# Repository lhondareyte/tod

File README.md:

## Top Octave Frequency generator

An  attempt to build a top octave divider. This can also be used to make any static prescaler.

## Restrictions

### DC Characteristics

Original MOSTEK chips require a supply voltage of ~15v (Max 16v). Input clock voltage must be between 0v and Vss -1v min. To avoid this, a TTL compatible master clock is include in schematic (Typical clock frequency is 2.00024 MHz).

### Duty cycle

MOSTEK chips differs in their number of dividers and duty cycle :

* MK50240 : 50% - 13 dividers (239 to 478)
* MK50241 : 30% - 13 dividers (239 to 478)
* MK50242 : 50% - 12 dividers (239 to 451)

This emulation only generate a (almost) 50% duty cycle. Thereby,  MK50241 model is not supported since the timbre will be affected. 

## Power consumption

Original MOSTEK chips sink 24mA@15V : 0.36w Typ. (Max 37mA@15V = 0.56W). You need 13 attiny4/13 to emulate a MK50240 (12 for a MK50242). Total power consumption for 13 ATtiny13 is about 30mA@5V (Not include clock circuitry).

## TODO

* Support 30% duty cycle

## Other use

The script `genedivider.pl` can be use to generate assembly code for any static prescaler. For example, to build a `by 42` prescaler:

    ./genedivider.pl 42 > divide.S

If an overflow/underflow occurs you can try to adjust `$loop` variable:

    ./genedivider.pl 10000 200 > divide.S

Warning, the script do not check the generated code size.

## Programming the attiny4

The ATtiny4 require a programmer that is compatible with the TPI mode (Tiny Programming Interface). 

To flash one divider with `avrdude`,  connect the attiny to the programmer as follow:

     USBASP               ATTINY
       +5v <-------------> +5v     (pin 5)
       gnd <-------------> gnd     (pin 2)
     reset <-------------> reset   (pin 6)
      MOSI <-------------> TPIDATA (pin 1)
       CLK <-------------> TPICLK  (pin 3)

then

    avrdude -c usbasp -p t4 -U flash:w:437.hex

and apply fuse configuration

    avrdude -c usbasp -p t4 -U BYTE0:w:0xfa:m

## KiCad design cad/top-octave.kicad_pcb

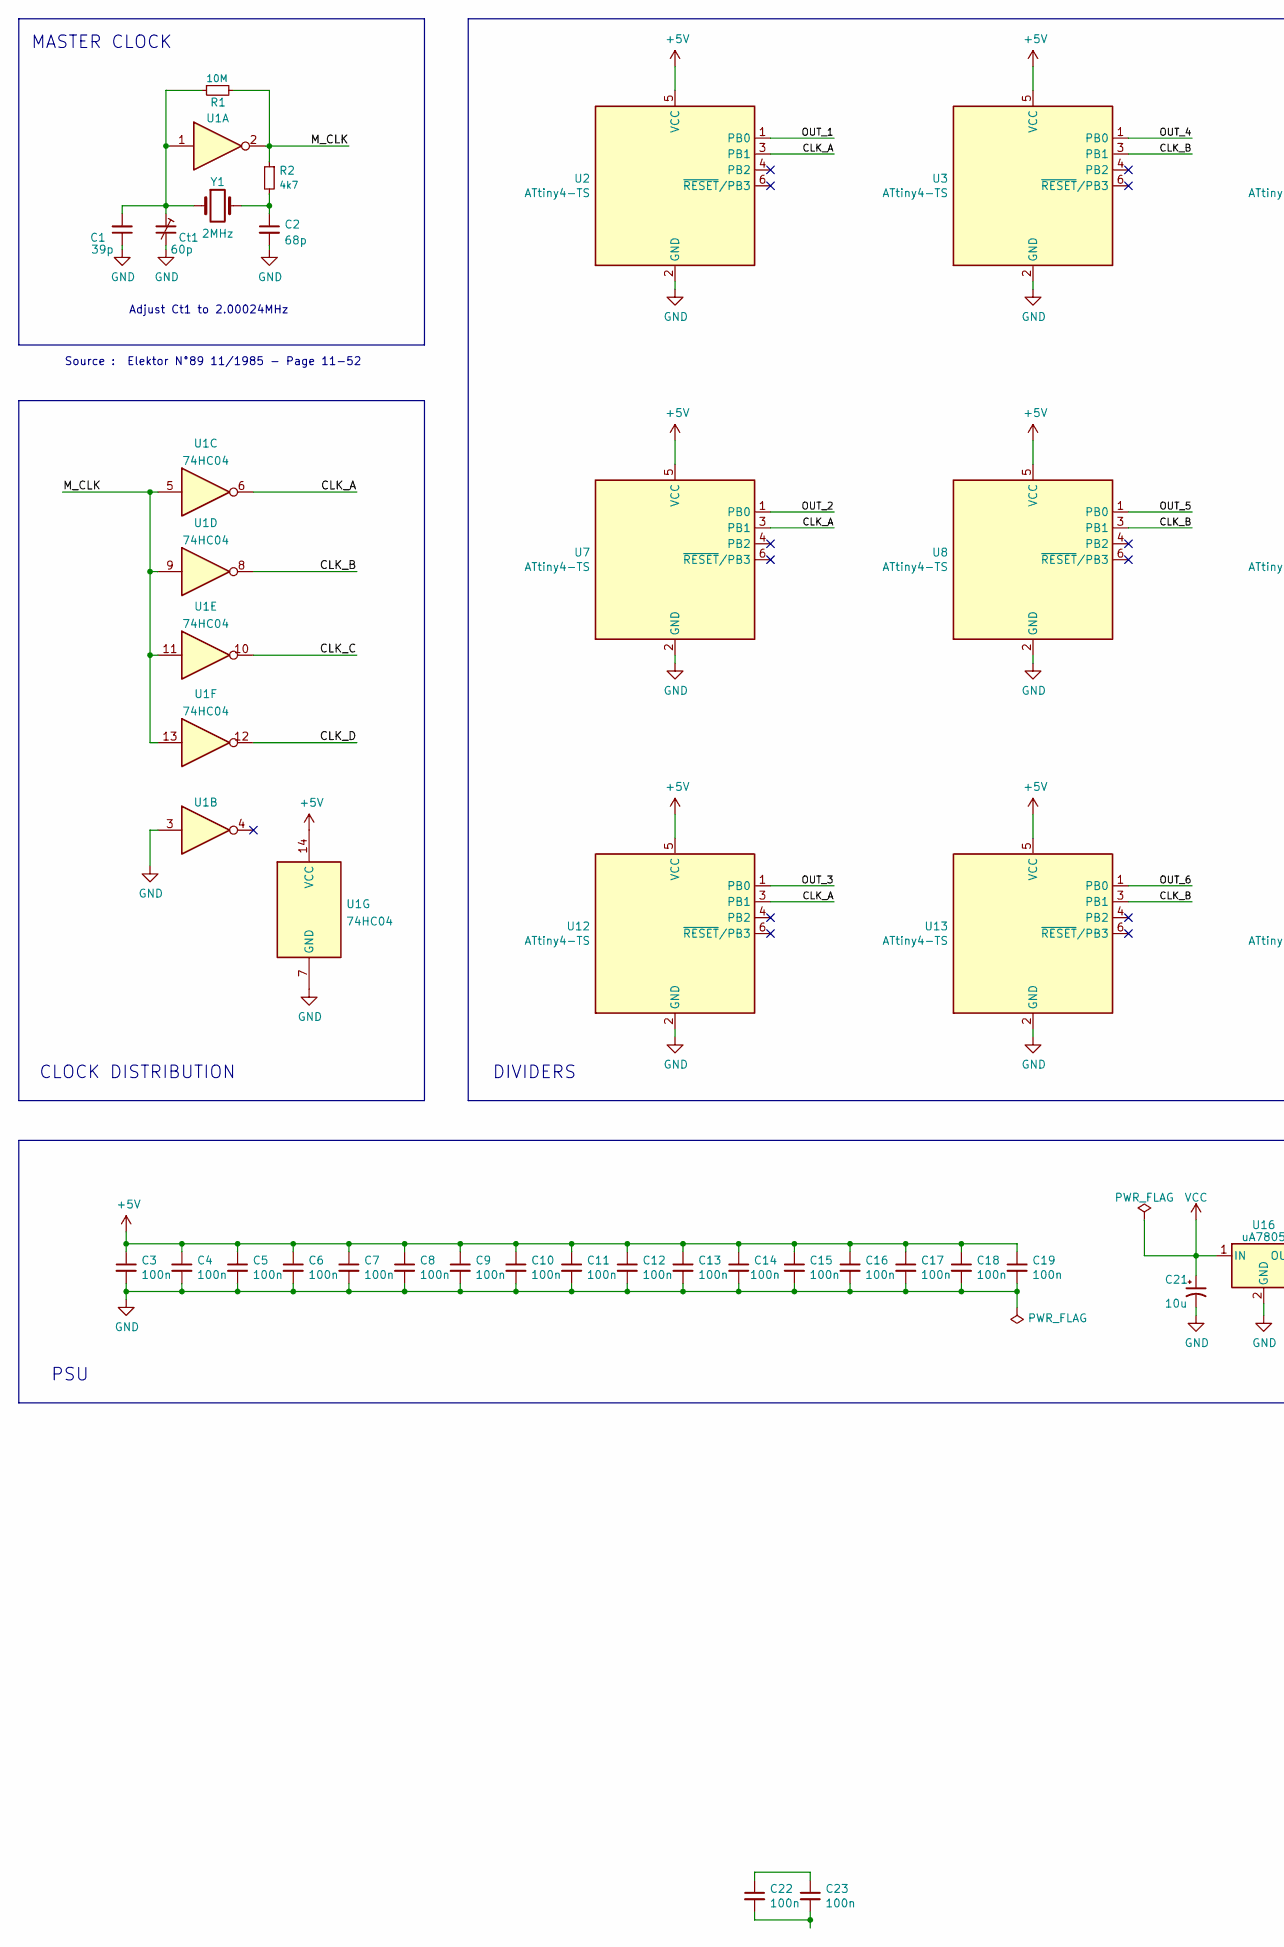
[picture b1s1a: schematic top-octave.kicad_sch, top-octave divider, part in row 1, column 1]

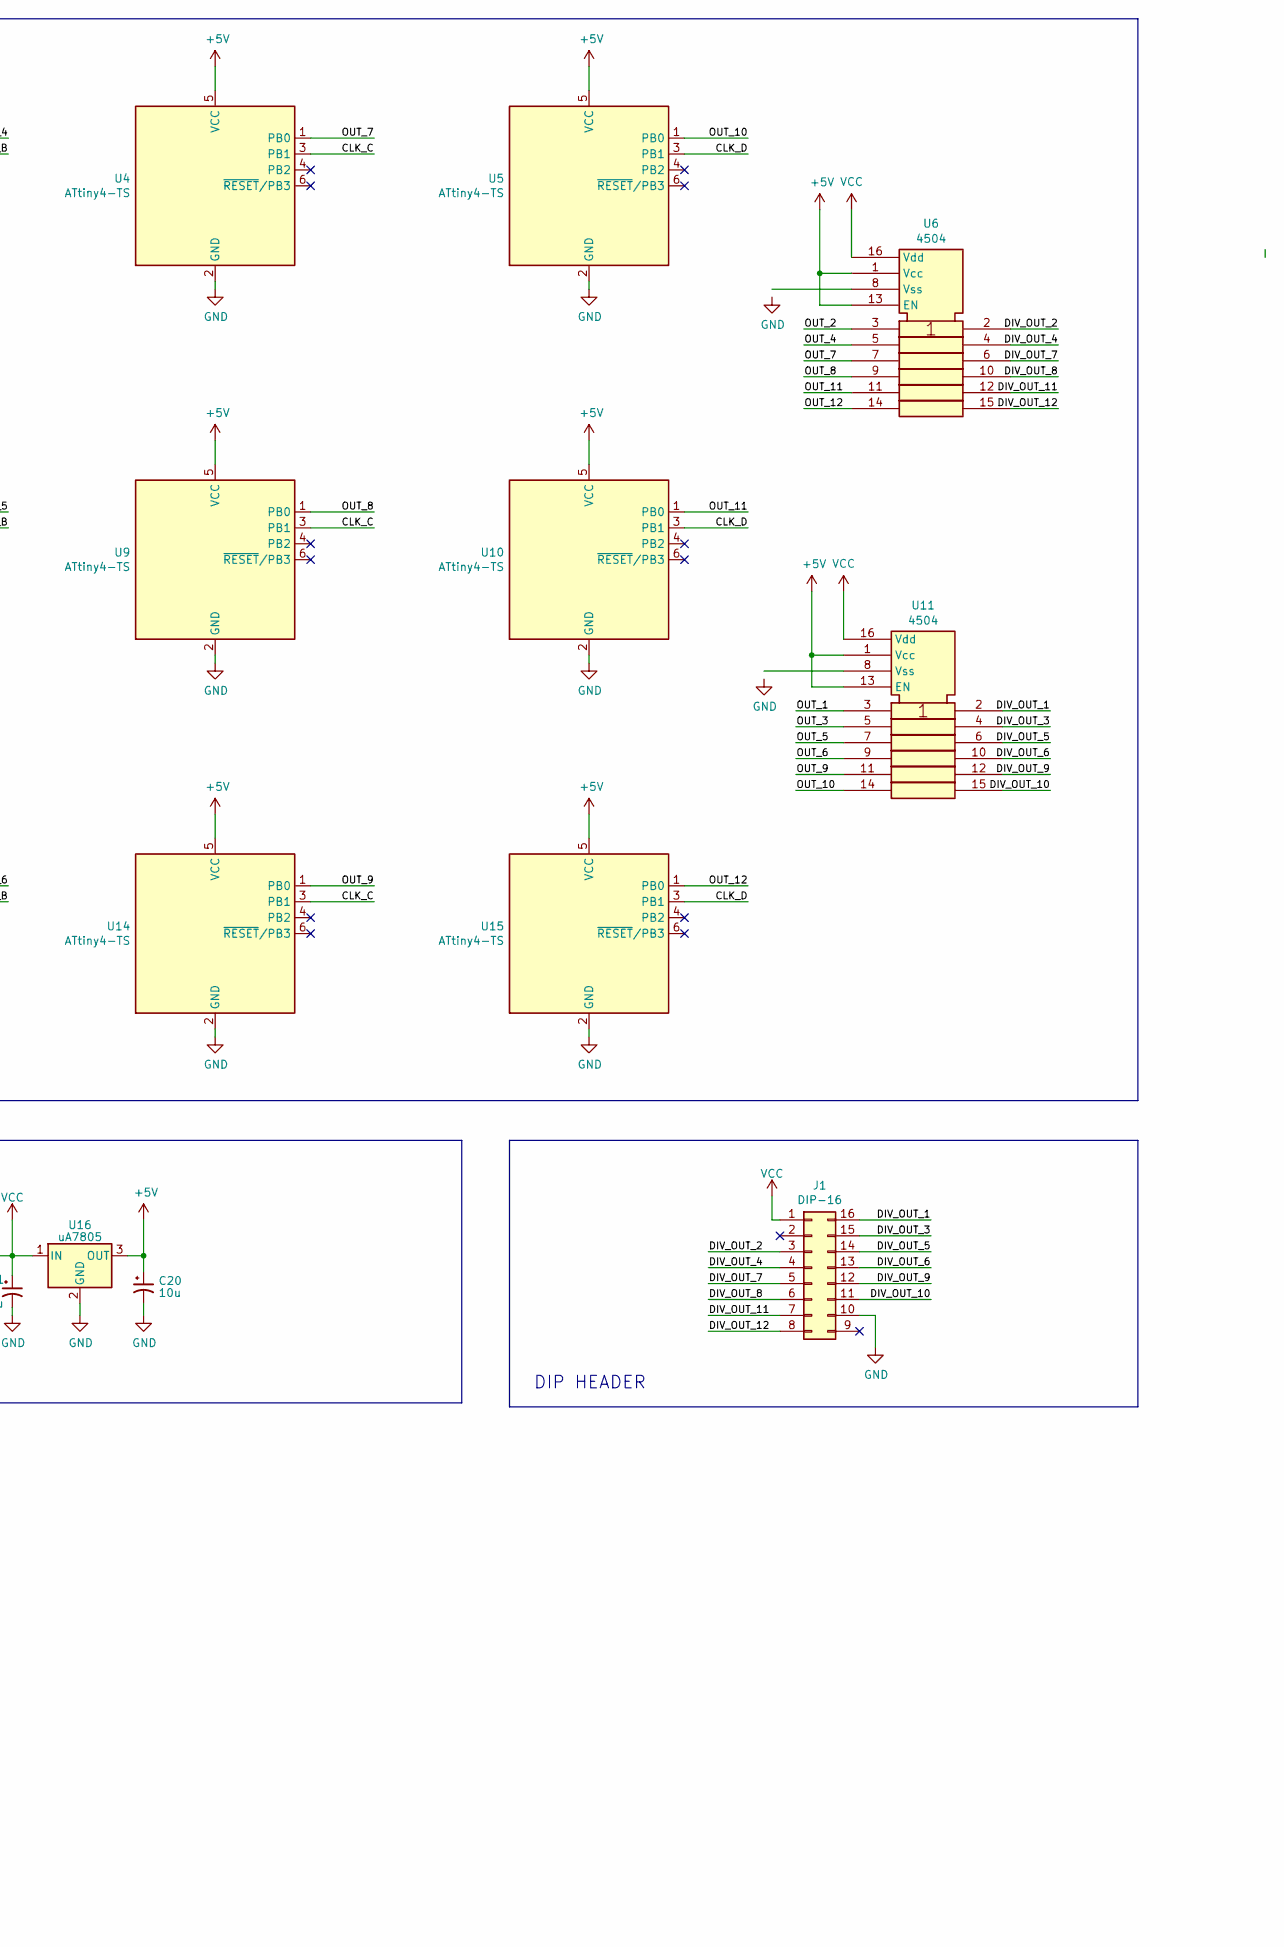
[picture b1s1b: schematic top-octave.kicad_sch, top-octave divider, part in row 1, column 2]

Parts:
C1: 39p; C_1206_3216Metric
C2: 68p; C_1206_3216Metric
C3, C4, C5, C6, C7, C8, C9, C10, C11, C12, C13, C14, C15, C16, C17, C18, C19, C22, C23: 100n; R_0805_2012Metric_Pad1.20x1.40mm_HandSolder
C20, C21: 10u
Ct1: 60p
J1: DIP-16; DIP-16_W7.62mm_Socket
R1: 10M; R_0805_2012Metric_Pad1.20x1.40mm_HandSolder
R2: 4k7; R_0805_2012Metric_Pad1.20x1.40mm_HandSolder
U1: 74HC04; SOIC-14_3.9x8.7mm_P1.27mm
U2, U3, U4, U5, U7, U8, U9, U10, U12, U13, U14, U15: ATtiny4-TS; SOT-23-6
U6, U11: 4504; SO-16_3.9x9.9mm_P1.27mm
U16: uA7805; SOT-223
Y1: 2MHz; SOT-89-5

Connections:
+5V: C3.1, C4.1, C5.1, C6.1, C7.1, C8.1, C9.1, C10.1, C11.1, C12.1, C13.1, C14.1, C15.1, C16.1, C17.1, C18.1, C19.1, C20.1, U1.14 (VCC), U2.5 (VCC), U3.5 (VCC), U4.5 (VCC), U5.5 (VCC), U6.1 (Vcc), U6.13 (EN), U7.5 (VCC), U8.5 (VCC), U9.5 (VCC), U10.5 (VCC), U11.1 (Vcc), U11.13 (EN), U12.5 (VCC), U13.5 (VCC), U14.5 (VCC), U15.5 (VCC), U16.3 (OUT)
/CLK_A: U1.6, U2.3 (PB1), U7.3 (PB1), U12.3 (PB1)
/CLK_B: U1.8, U3.3 (PB1), U8.3 (PB1), U13.3 (PB1)
/CLK_C: U1.10, U4.3 (PB1), U9.3 (PB1), U14.3 (PB1)
/CLK_D: U1.12, U5.3 (PB1), U10.3 (PB1), U15.3 (PB1)
/DIV_OUT_1: J1.16, U11.2
/DIV_OUT_2: J1.3, U6.2
/DIV_OUT_3: J1.15, U11.4
/DIV_OUT_4: J1.4, U6.4
/DIV_OUT_5: J1.14, U11.6
/DIV_OUT_6: J1.13, U11.10
/DIV_OUT_7: J1.5, U6.6
/DIV_OUT_8: J1.6, U6.10
/DIV_OUT_9: J1.12, U11.12
/DIV_OUT_10: J1.11, U11.15
/DIV_OUT_11: J1.7, U6.12
/DIV_OUT_12: J1.8, U6.15
/M_CLK: R1.2, R2.1, U1.2, U1.5, U1.9, U1.11, U1.13
/OUT_1: U2.1 (PB0), U11.3
/OUT_2: U6.3, U7.1 (PB0)
/OUT_3: U11.5, U12.1 (PB0)
/OUT_4: U3.1 (PB0), U6.5
/OUT_5: U8.1 (PB0), U11.7
/OUT_6: U11.9, U13.1 (PB0)
/OUT_7: U4.1 (PB0), U6.7
/OUT_8: U6.9, U9.1 (PB0)
/OUT_9: U11.11, U14.1 (PB0)
/OUT_10: U5.1 (PB0), U11.14
/OUT_11: U6.11, U10.1 (PB0)
/OUT_12: U6.14, U15.1 (PB0)
GND: C1.1, C2.2, C3.2, C4.2, C5.2, C6.2, C7.2, C8.2, C9.2, C10.2, C11.2, C12.2, C13.2, C14.2, C15.2, C16.2, C17.2, C18.2, C19.2, C20.2, C21.2, Ct1.2, J1.10, U1.3, U1.7 (GND), U2.2 (GND), U3.2 (GND), U4.2 (GND), U5.2 (GND), U7.2 (GND), U8.2 (GND), U9.2 (GND), U10.2 (GND), U12.2 (GND), U13.2 (GND), U14.2 (GND), U15.2 (GND), U16.2 (GND)
unnamed: C1.2, Ct1.1, R1.1, U1.1, Y1.1
unnamed: C2.1, R2.2, Y1.2
unnamed: C22.1, C23.1
unnamed: C22.2, C23.2
VCC: C21.1, J1.1, U6.16 (Vdd), U11.16 (Vdd), U16.1 (IN)

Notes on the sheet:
MASTER CLOCK
DIVIDERS
DIP HEADER
Adjust Ct1 to 2.00024MHz
PSU
Source : Elektor N°89 11/1985 - Page 11-52
CLOCK DISTRIBUTION

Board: 2 copper layers, 41 parts (0 on the bottom side), 36 nets, no tracks yet.

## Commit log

2018-05-24 Initial commit with skeleton files
2020-05-10 Using one attiny per divider.
2020-07-17 Add .gitignore and README.md
2020-08-05 Set prescaler for external clock.
2020-08-07 Cleanup Makefile
2020-08-07 Add some comments
2020-08-30 Almost works on atmega328p
2020-08-30 Update Makefile
2020-08-30 Adding some references
2020-08-30 Add .gitattributes
2020-08-31 Update copyright
2020-09-23 wrong shebang
2020-09-23 Update "all" target
2020-09-25 Specific prescaler only for attiny4
2020-09-25 Using wait loop to reduce text size for attiny.
2021-01-11 Generic makefile
2021-01-12 Remove more GNUism
2021-02-10 Update Makefile.
2021-02-10 Add debug option and clarify variables names
2021-06-09 Create LICENSE
2021-08-07 Adding a config file per mcu
2021-10-20 Update LICENSE
2022-02-23 Fix asm target
2022-02-23 Update debug mode
2022-08-19 Import KiCad files
2022-11-19 Add Mostek datasheet for reference
2022-11-19 Update schematic
2022-11-25 Fix level shifter
2024-04-21 Refactoring Makefiles and add attiny13a config file
2024-04-26 Set external clock for attiny4
2024-04-26 Update License header
2024-04-26 Fix inconsistent timing
2024-04-27 Fix wrong header for MK50242
2024-04-29 Fix timing and duty cycle (49.79%)
2024-04-29 Fix wrong message
2024-11-30 gstabs switch is no longer supported
2024-11-30 Add more datasheets
2025-03-14 Add loop option for static prescaler
2025-03-15 Replace all mosfet by 2 cd4504
2025-11-20 Fix external clock settings on attiny4
2025-11-25 Fix wrong word parity -> even
2025-12-03 Remove unused targets
2026-02-17 Ignore *.kicad_prl
